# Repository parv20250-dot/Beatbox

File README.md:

# Beatbox
Welcome to the land of music and dreams (hopefully not nightmares). Here you see me try my hand at making a drum pad.

(note: the colour can be selected/altered on the pcb manufacturer's app)

## **<ins>#Basic functioning</ins>**

The drum pad detects when it is hit using Piezo discs which are basically small discs that can measure changes in pressure or vibration through the piezoelectric effect. When you strike the pad the force flexes the internal ceramic element inside the piezo disc creating an electrical signal. This is used to sense when it is hit and also the intensity of the hit through the vibrations caused on impact.

This information is send to the ESP-32-C3-Supermini which then computes what sound to play and how loud to play it and sends this information or audio data to the Amplifier module. The amplifier module then converts this information/audio data to playable audio and sends it to the speaker resulting in sound being played. 

There is also protective equipment such as resistors and diodes, which can be observed in the schematic below.

## **<ins>LIGHT</ins>**

The lighting system works mostly separate of the sound system. The WS2812(12 Bit LED ring) is connected to the ESP32-C3-SuperMini. When the Piezo disc detects a hit, the ESP simultaneously sends audio data to the Amplifier module and lighting data to the LED's. The LED rings are connected in series allowing for the lighting information to be passed along the LED rings in order to make the corresponding ring light up. There is a level shifter in between as the LED's require a 5v input whereas the ESP only outputs 3.3V of current. 

## **<ins>POWER</ins>**

The whole system is powered via USB-C input on the ESP.

## **<ins>SPECIAL EFFECT-</ins>**

When the Piezo discs are hit in a particular order within a predefined time frame, it plays a special long sound effect and lights up all four LED's.

## **<ins>FIRMWARE-</ins>**

The firmware is written in c++ for the ESP-32-C3 and compiled in Arduino. It basically detects inputs from the piezo sensors and uses the intensity of the vibrations of the Piezo buzzer and in turn the hit to trigger drum sound responses through the speaker. It also controls the LED rings and the disc being hit lights up. The code sets different colors for every disc/pad with pad 1 being red, pad 2 being green, pad 3 being blue, pad 4 being orange. The brightness of the LED depends on hit intensity. When 4 of the pads are hit in a particular order (1->2->3->4) it plays special sound within an 8 second time frame). The code also has parts for calibration and checking that all the parts are connected and working properly. The longggg groups of numbers that you see in the code file are audio that have been converted into text format as 16 bit arrays.

## **<ins> BOM <ins>**

|Item                                                   |Qty|Supplier   |Cost/item|Total Cost|link                                                                            |
|-------------------------------------------------------|---|-----------|---------|----------|--------------------------------------------------------------------------------|
|pcb                                                    |1  |jlcpcb     |$1.50    |$1.50     |https://jlcpcb.com/                                                             |
|ESP-32-C3 Supermini                                    |1  |Ali Express|$4.80    |$4.80     |https://a.aliexpress.com/_EvaAqpy                                               |
|Max 98357A                                             |1  |Ali Express|$3.70    |$3.70     |https://a.aliexpress.com/_EHFUNMI                                               |
|10k ohm resistors                                      |1  |electro:kit|$0.10    |$0.10     |https://www.electrokit.com/motstand-kolfilm-0.25w-10kohm-10k                    |
|1M resistors                                           |1  |electro:kit|$0.10    |$0.10     |https://www.electrokit.com/motstand-kolfilm-0.25w-1mohm-1m                      |
|Piezo discs (20mm)                                     |5  |electro:kit|$0.45    |$2.25     |https://www.electrokit.com/piezoelement-20mm                                    |
|Miniature Speaker                                      |1  |electro:kit|$2.80    |$2.80     |https://www.electrokit.com/miniatyrhogtalare-8ohm-2w-20x30x6.8mm                |
|BAT85 DO-35 30V 200mA Diode                            |1  |electro:kit|$1.50    |$1.50     |https://www.electrokit.com/bat85-do-35-30v-200ma                                |
|74AHCT125N level converter                             |1  |electro:kit|$0.90    |$0.90     |https://www.electrokit.com/sn74ahct125n-dip-14-quad-buffer                      |
|Electrolytic capacitor 1000uF 6.3V 105C ø8x11.5mm 6000h|1  |electro:kit|$0.90    |$0.90     |https://www.electrokit.com/elektrolytkondensator-1000uf-6.3v-105c-8x11.5mm-6000h|
|WS2812 LED                                             |4  |Ali Express|$1.80    |$7.20     |https://a.aliexpress.com/_EvkmW82                                               |
|Connecting wire 0.26mm² single-wire - red /m           |1  |electro:kit|$0.90    |$0.90     |https://www.electrokit.com/kopplingstrad-0.28mm2-entradig-rod-/m                |
|Connecting wire 0.5mm² single-wire - black             |1  |electro:kit|$0.90    |$0.90     |https://www.electrokit.com/kopplingstrad-awg20-entradig-svart-/m                |
|Estimated total shipping                               |1  |           |         |$4.90     |                                                                                |

## **<ins>Credits-</ins>**

This project has been inspired by several different drum pad projects online, however, the design, pcb layout and firmware are all my own. This project was made as a part of the Half Life event by Hack Club.

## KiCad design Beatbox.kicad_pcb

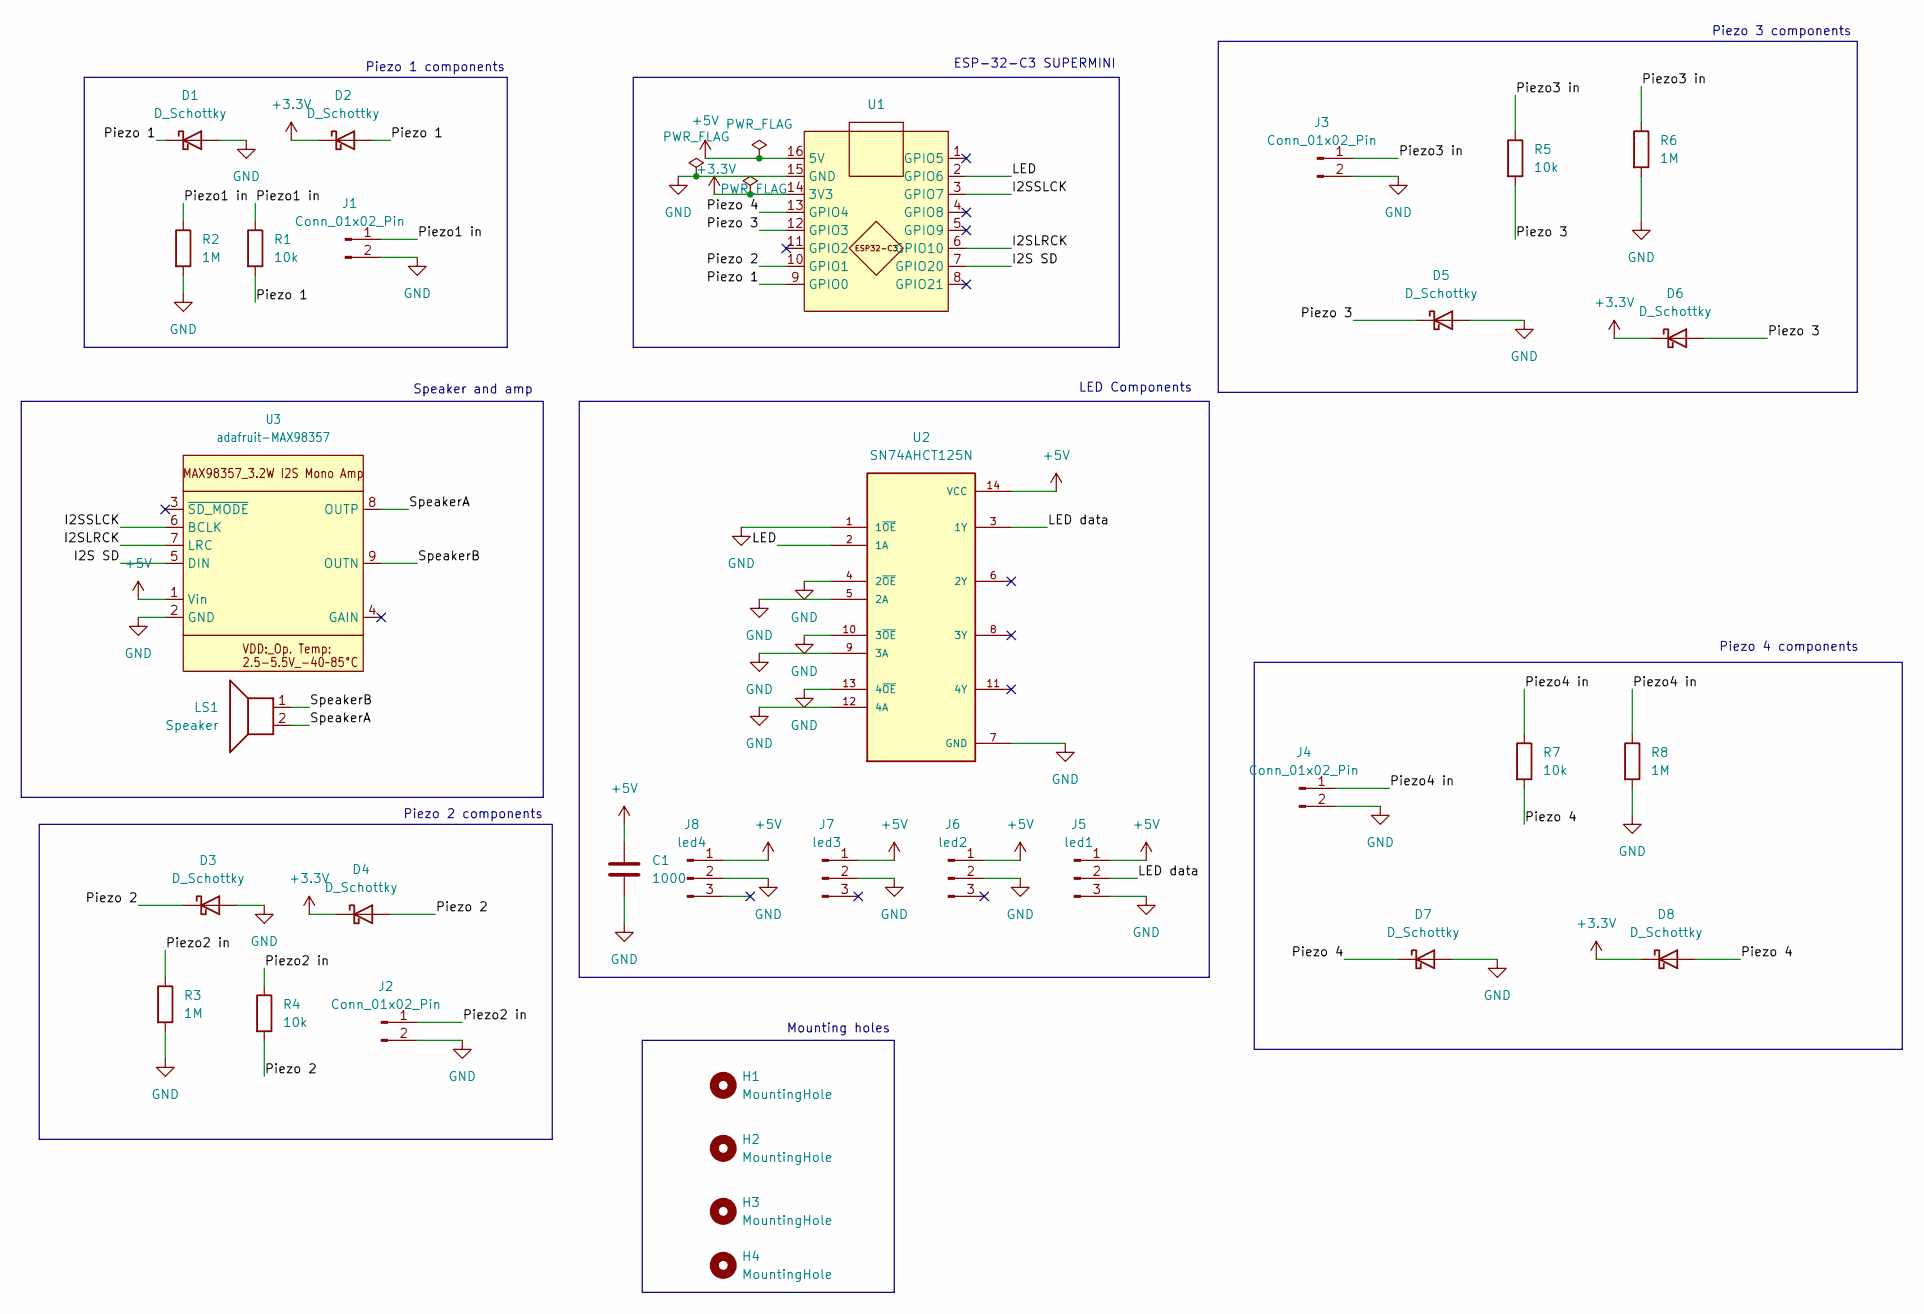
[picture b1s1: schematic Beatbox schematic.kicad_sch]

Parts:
C1: 1000; CP_Radial_D8.0mm_P3.50mm
D1, D2, D3, D4, D5, D6, D7, D8: D_Schottky; D_DO-34_SOD68_P7.62mm_Horizontal
H1, H2, H3, H4: MountingHole; MountingHole_3.2mm_M3
J1, J2, J3, J4: Conn_01x02_Pin; PinHeader_1x02_P2.54mm_Vertical
J5: led1; PinHeader_1x03_P2.54mm_Vertical
J6: led2; PinHeader_1x03_P2.54mm_Vertical
J7: led3; PinHeader_1x03_P2.54mm_Vertical
J8: led4; PinHeader_1x03_P2.54mm_Vertical
LS1: Speaker; PinHeader_1x02_P2.54mm_Vertical
R1, R4, R5, R7: 10k; R_Axial_DIN0207_L6.3mm_D2.5mm_P7.62mm_Horizontal
R2, R3, R6, R8: 1M; R_Axial_DIN0207_L6.3mm_D2.5mm_P7.62mm_Horizontal
U1: COMM-SMD_16P-L22.5-W18.0-P2.54-TL
U2: SN74AHCT125N; DIP794W45P254L1930H508Q14; PARTREV Q
U3: adafruit-MAX98357

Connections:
+3.3V: D2.1 (K), D4.1 (K), D6.1 (K), D8.1 (K), U1.14 (3V3)
+5V: C1.1, J5.1, J6.1, J7.1, J8.1, U1.16 (5V), U2.14 (VCC), U3.1 (Vin)
/I2S SD: U1.7 (GPIO20), U3.5 (DIN)
/I2SLRCK: U1.6 (GPIO10), U3.7 (LRC)
/I2SSLCK: U1.3 (GPIO7), U3.6 (BCLK)
/LED: U1.2 (GPIO6), U2.2 (1A)
/LED data: J5.2, U2.3 (1Y)
/Piezo1 in: J1.1, R1.1, R2.1
/Piezo2 in: J2.1, R3.1, R4.1
/Piezo3 in: J3.1, R5.1, R6.1
/Piezo4 in: J4.1, R7.1, R8.1
/Piezo 1: D1.1 (K), D2.2 (A), R1.2, U1.9 (GPIO0)
/Piezo 2: D3.1 (K), D4.2 (A), R4.2, U1.10 (GPIO1)
/Piezo 3: D5.1 (K), D6.2 (A), R5.2, U1.12 (GPIO3)
/Piezo 4: D7.1 (K), D8.2 (A), R7.2, U1.13 (GPIO4)
/SpeakerA: LS1.2, U3.8 (OUTP)
/SpeakerB: LS1.1, U3.9 (OUTN)
GND: C1.2, D1.2 (A), D3.2 (A), D5.2 (A), D7.2 (A), J1.2, J2.2, J3.2, J4.2, J5.3, J6.2, J7.2, J8.2, R2.2, R3.2, R6.2, R8.2, U1.15 (GND), U2.1 (1~OE), U2.4 (2~OE), U2.5 (2A), U2.7 (GND), U2.9 (3A), U2.10 (3~OE), U2.12 (4A), U2.13 (4~OE), U3.2 (GND)

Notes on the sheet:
Speaker and amp
LED Components
Piezo 2 components
ESP-32-C3 SUPERMINI
Mounting holes
Piezo 3 components
Piezo 4 components
Piezo 1 components

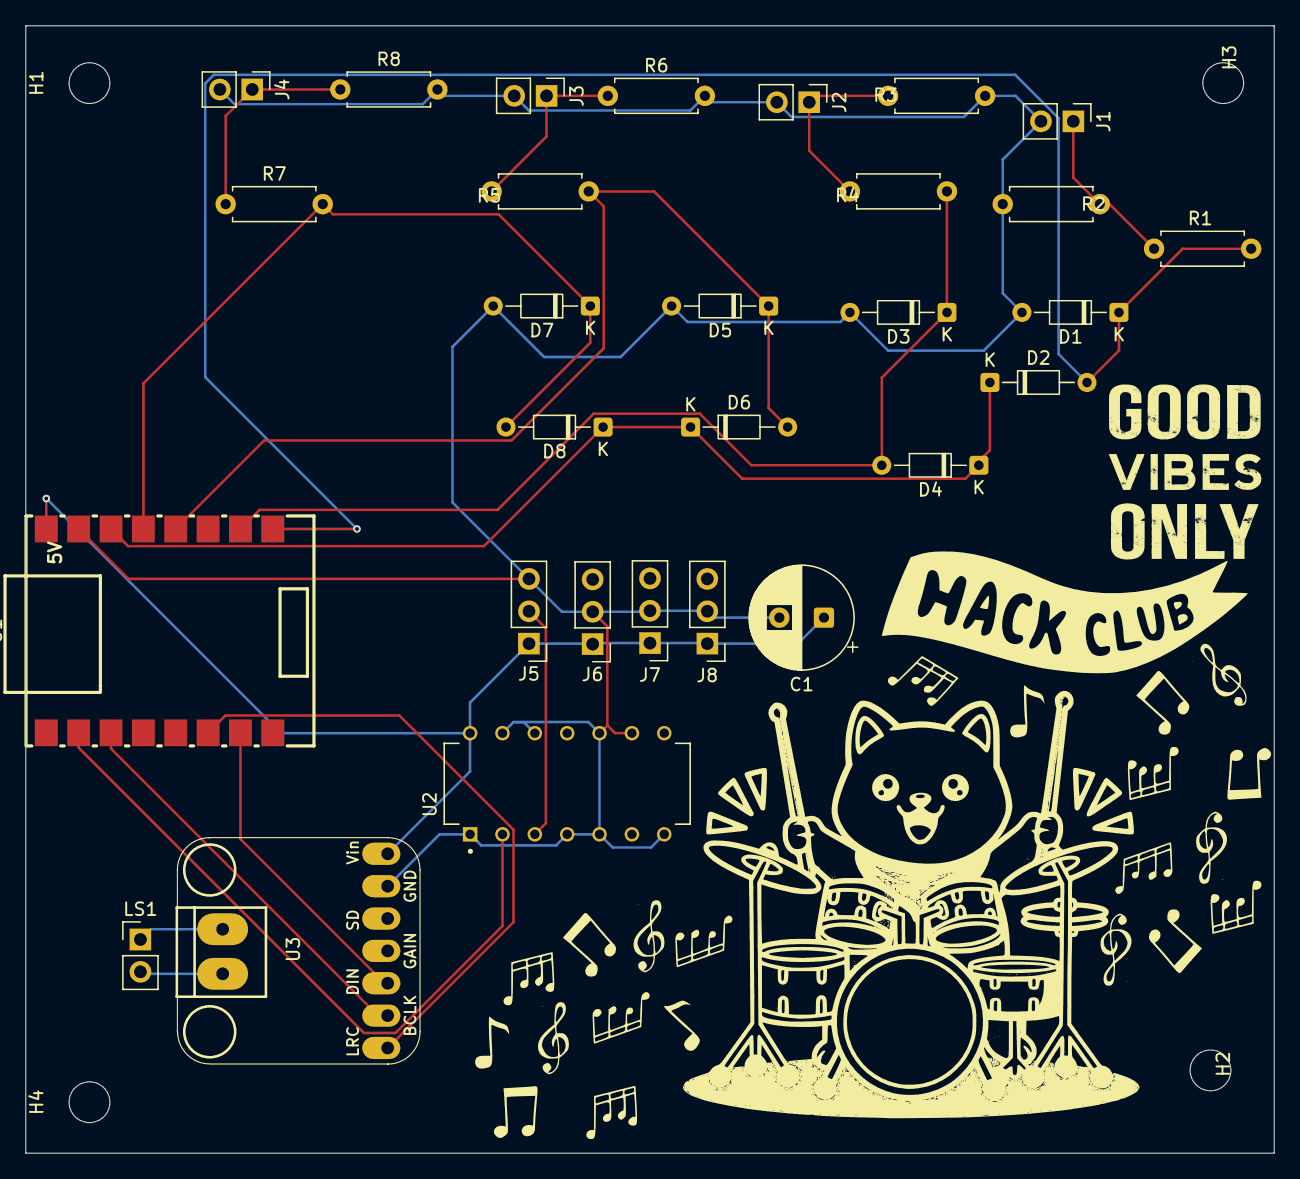
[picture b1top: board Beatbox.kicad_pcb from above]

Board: 2 copper layers, 98.0 x 88.5 mm, 33 parts (0 on the bottom side), 18 nets.
